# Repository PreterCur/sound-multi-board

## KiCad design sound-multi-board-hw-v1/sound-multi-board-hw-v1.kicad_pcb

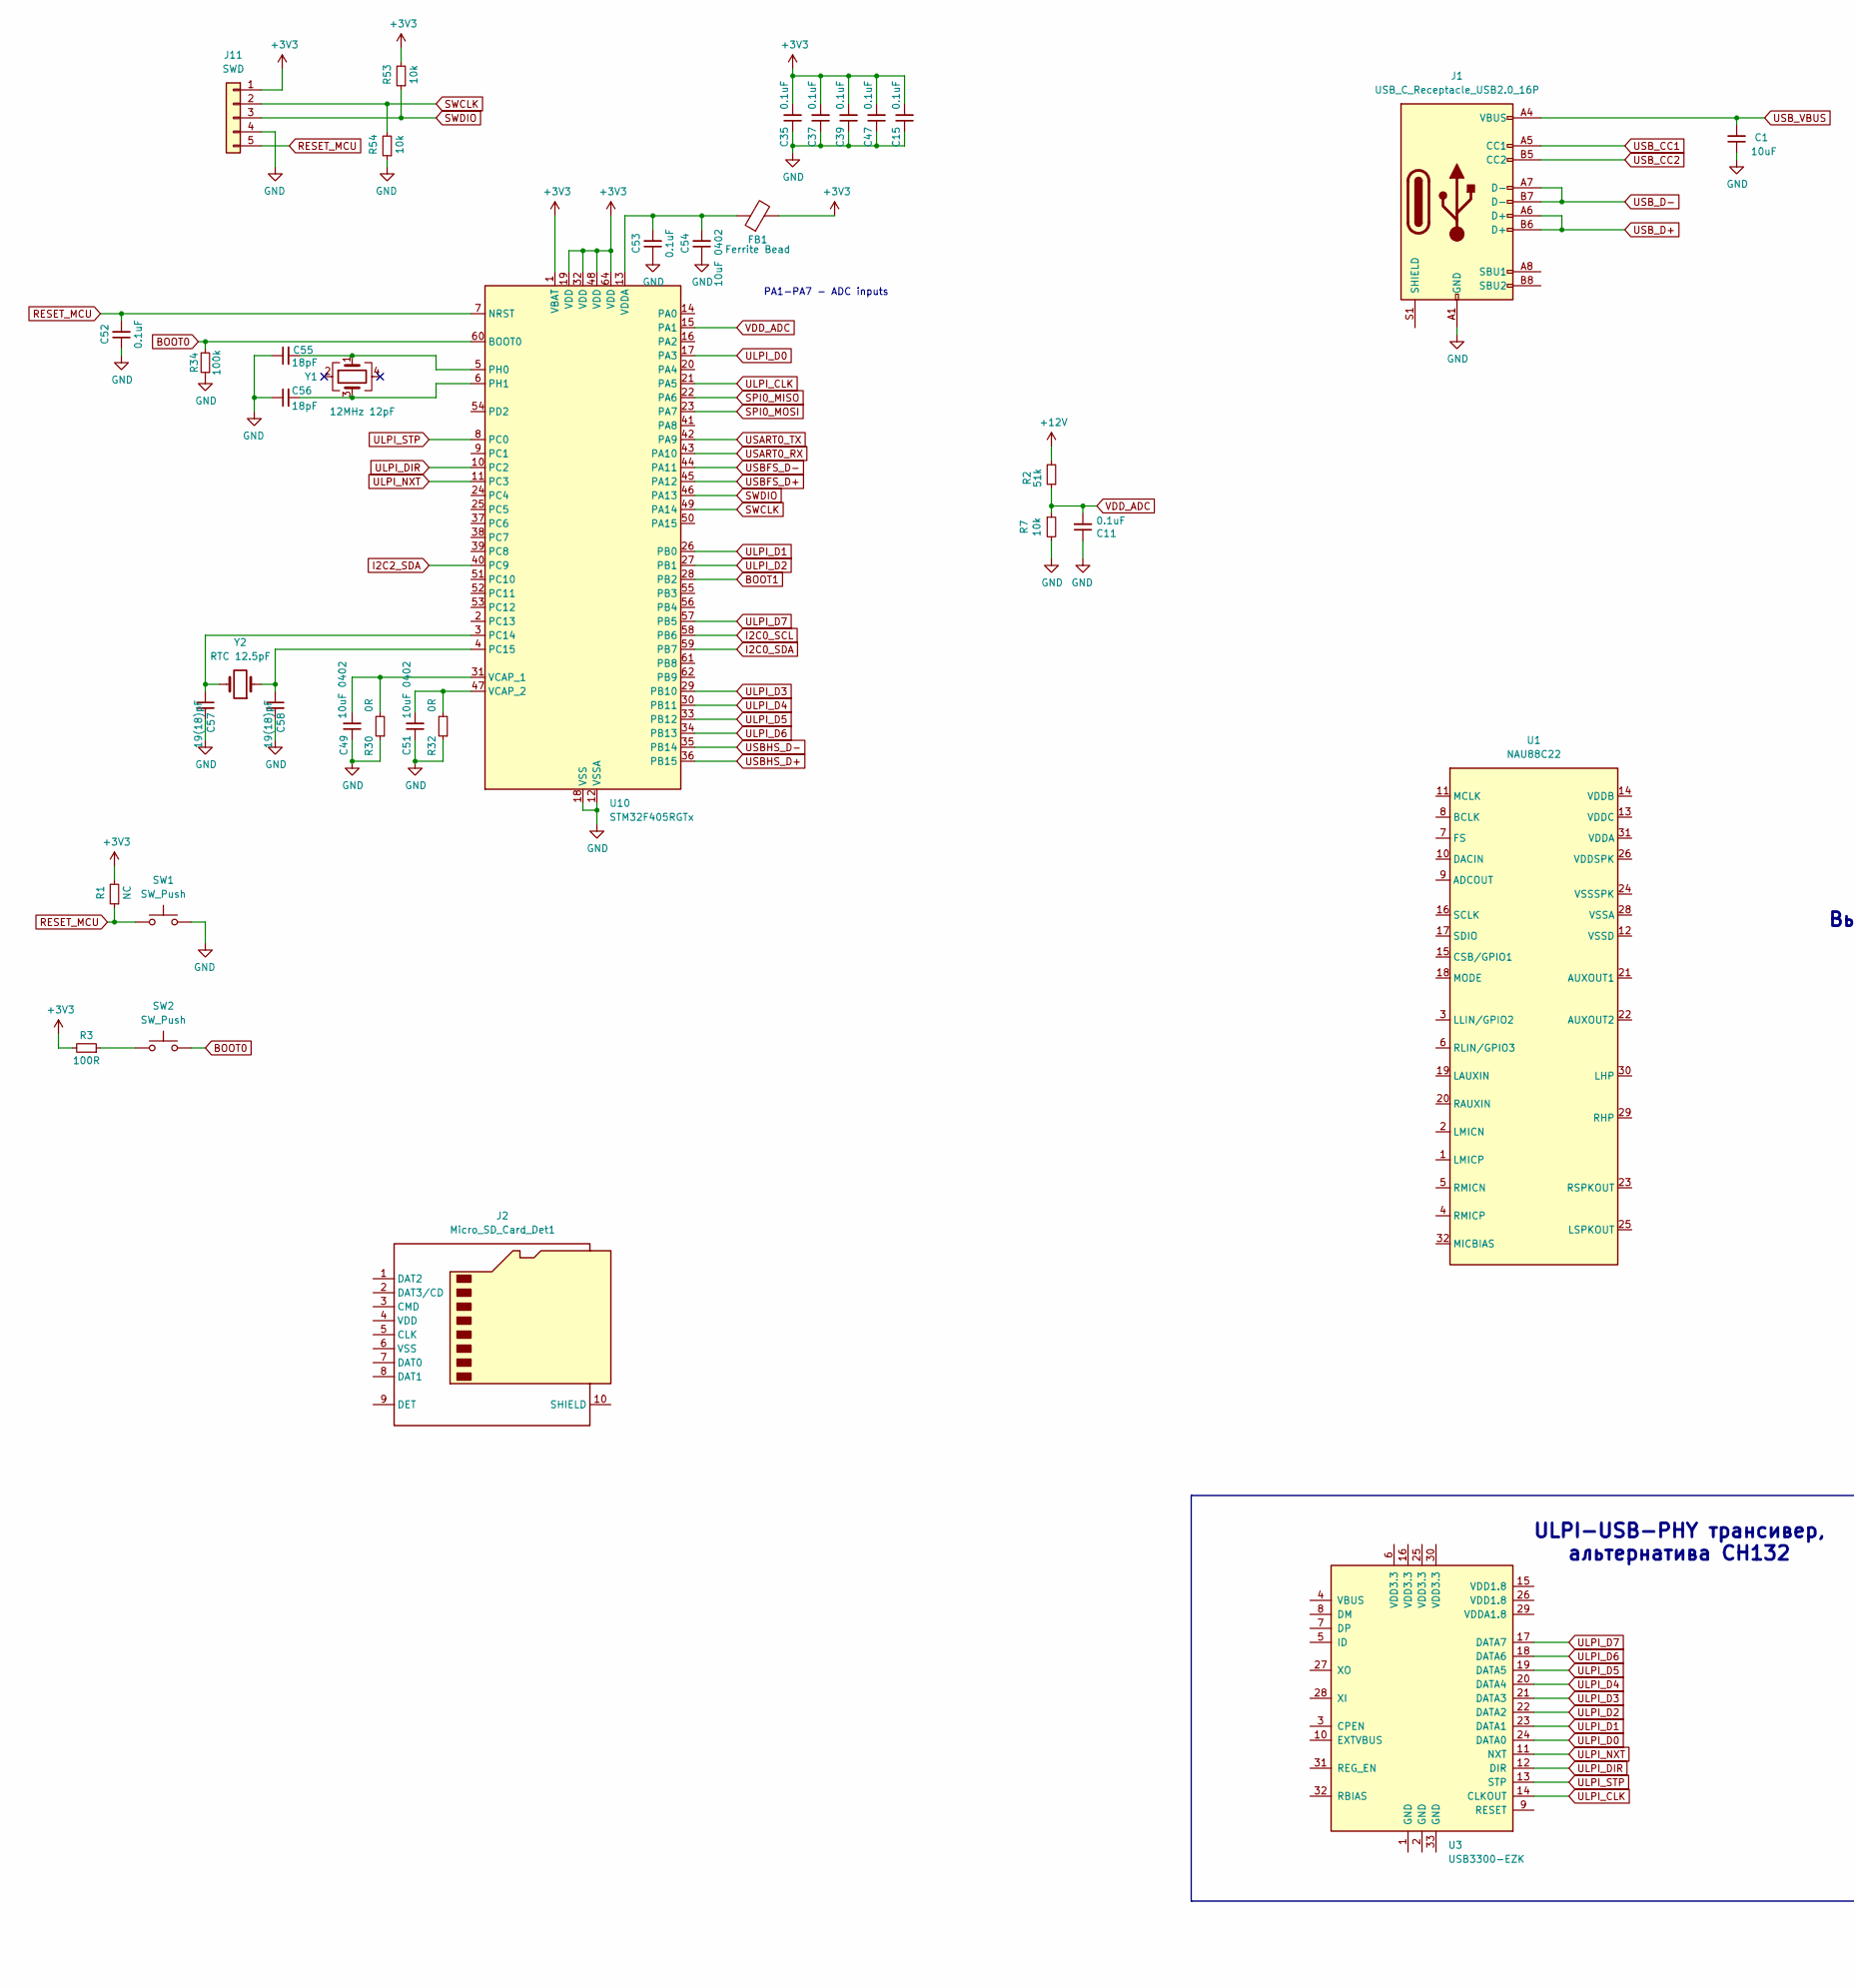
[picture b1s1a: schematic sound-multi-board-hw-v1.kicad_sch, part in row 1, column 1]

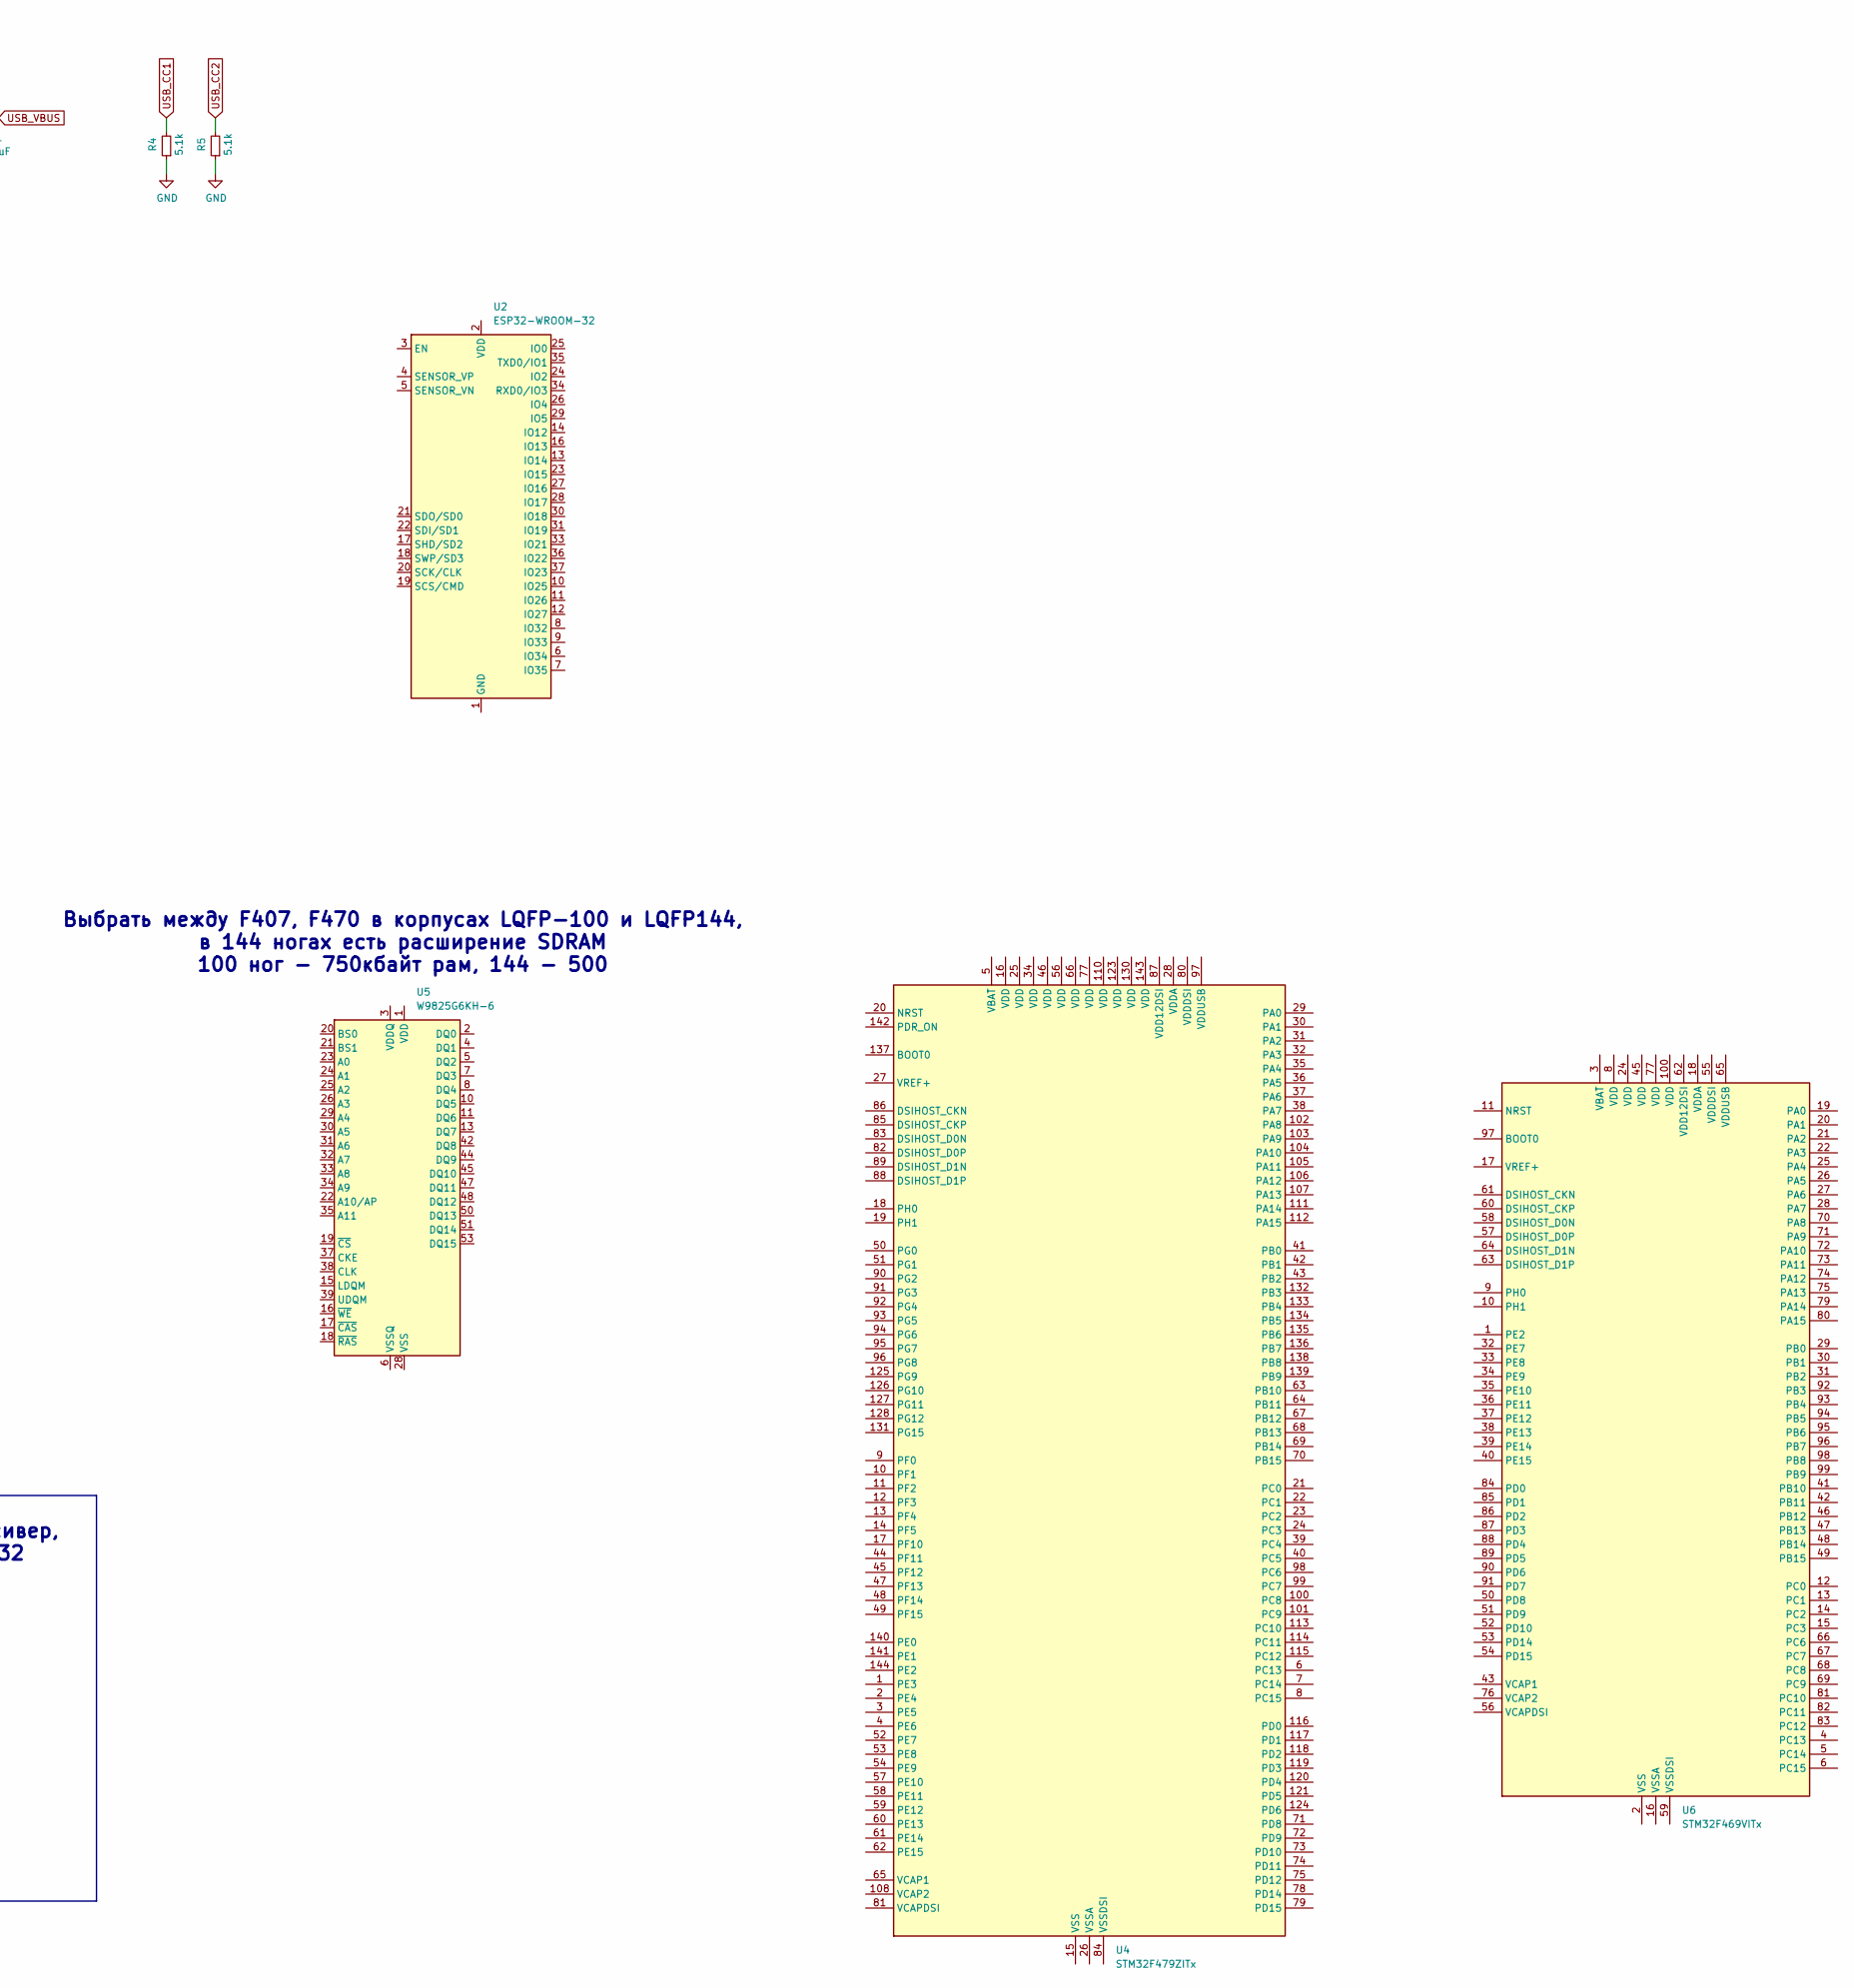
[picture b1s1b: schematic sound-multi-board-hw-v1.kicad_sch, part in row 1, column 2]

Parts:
C1: 10uF; C_0603_1608Metric
C11, C15, C35, C37, C39, C47, C52, C53: 0.1uF; C_0402_1005Metric
C49, C51, C54: 10uF 0402; C_0402_1005Metric
C55, C56: 18pF; C_0402_1005Metric
C57, C58: 19(18)pF; C_0402_1005Metric
FB1: Ferrite Bead; L_0402_1005Metric
J1: USB_C_Receptacle_USB2.0_16P; USB_C_Receptacle_XKB_U262-16XN-4BVC11
J2: Micro_SD_Card_Det1
J11: SWD; PinHeader_1x05_P1.27mm_Vertical
R1: NC; R_0402_1005Metric
R2: 51k; R_0402_1005Metric
R3: 100R; R_0402_1005Metric
R4, R5: 5.1k; R_0402_1005Metric
R7, R53, R54: 10k; R_0402_1005Metric
R30, R32: 0R; R_0402_1005Metric
R34: 100k; R_0402_1005Metric
SW1, SW2: SW_Push
U1: NAU88C22; LFCSP-32-1EP_5x5mm_P0.5mm_EP3.5x3.5mm_ThermalVias
U2: ESP32-WROOM-32
U3: USB3300-EZK; QFN-32-1EP_5x5mm_P0.5mm_EP3.45x3.45mm
U4: STM32F479ZITx; LQFP-144_20x20mm_P0.5mm
U5: W9825G6KH-6; TSOP-II-54_22.2x10.16mm_P0.8mm
U6: STM32F469VITx; LQFP-100_14x14mm_P0.5mm
U10: STM32F405RGTx; LQFP-64_10x10mm_P0.5mm
Y1: 12MHz 12pF; Crystal_SMD_3225-4Pin_3.2x2.5mm
Y2: RTC 12.5pF; Crystal_SMD_3215-2Pin_3.2x1.5mm

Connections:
+3V3: C15.2, C35.2, C37.2, C39.2, C47.2, FB1.2, J11.1, R1.2, R3.2, R53.2, U10.1 (VBAT), U10.19 (VDD), U10.32 (VDD), U10.48 (VDD), U10.64 (VDD)
+12V: R2.2
BOOT0: R34.2, SW2.2, U10.60 (BOOT0)
BOOT1: U10.28 (PB2)
GND: C1.1, C11.1, C15.1, C35.1, C37.1, C39.1, C47.1, C49.1, C51.1, C52.1, C53.1, C54.1, C55.1, C56.1, C57.2, C58.2, J1.A1 (GND), J1.A12 (GND), J1.B1 (GND), J1.B12 (GND), J11.4, R4.1, R5.1, R7.2, R30.1, R32.1, R34.1, R54.1, SW1.2, U10.12 (VSSA), U10.18 (VSS), U10.63 (VSS)
I2C0_SCL: U10.58 (PB6)
I2C0_SDA: U10.59 (PB7)
I2C2_SDA: U10.40 (PC9)
unnamed: R3.1, SW2.1
unnamed: U2.1 (GND), U2.15 (GND), U2.38 (GND), U2.39 (GND)
unnamed: U4.15 (VSS), U4.33 (VSS), U4.55 (VSS), U4.76 (VSS), U4.109 (VSS), U4.122 (VSS), U4.129 (VSS)
unnamed: U5.1 (VDD), U5.14 (VDD), U5.27 (VDD)
unnamed: U5.3 (VDDQ), U5.9 (VDDQ), U5.43 (VDDQ), U5.49 (VDDQ)
unnamed: U5.28 (VSS), U5.41 (VSS), U5.54 (VSS)
unnamed: U5.6 (VSSQ), U5.12 (VSSQ), U5.46 (VSSQ), U5.52 (VSSQ)
unnamed: U6.2 (VSS), U6.7 (VSS), U6.23 (VSS), U6.44 (VSS), U6.78 (VSS)
unnamed: C57.1, U10.3 (PC14), Y2.2
unnamed: C58.1, U10.4 (PC15), Y2.1
unnamed: C55.2, U10.5 (PH0), Y1.1
unnamed: C56.2, U10.6 (PH1), Y1.3
unnamed: C49.2, R30.2, U10.31 (VCAP_1)
unnamed: C51.2, R32.2, U10.47 (VCAP_2)
unnamed: C53.2, C54.2, FB1.1, U10.13 (VDDA)
RESET_MCU: C52.2, J11.5, R1.1, SW1.1, U10.7 (NRST)
SPI0_MISO: U10.22 (PA6)
SPI0_MOSI: U10.23 (PA7)
SWCLK: J11.2, R54.2, U10.49 (PA14)
SWDIO: J11.3, R53.1, U10.46 (PA13)
ULPI_CLK: U3.14 (CLKOUT), U10.21 (PA5)
ULPI_D0: U3.24 (DATA0), U10.17 (PA3)
ULPI_D1: U3.23 (DATA1), U10.26 (PB0)
ULPI_D2: U3.22 (DATA2), U10.27 (PB1)
ULPI_D3: U3.21 (DATA3), U10.29 (PB10)
ULPI_D4: U3.20 (DATA4), U10.30 (PB11)
ULPI_D5: U3.19 (DATA5), U10.33 (PB12)
ULPI_D6: U3.18 (DATA6), U10.34 (PB13)
ULPI_D7: U3.17 (DATA7), U10.57 (PB5)
ULPI_DIR: U3.12 (DIR), U10.10 (PC2)
ULPI_NXT: U3.11 (NXT), U10.11 (PC3)
ULPI_STP: U3.13 (STP), U10.8 (PC0)
USART0_RX: U10.43 (PA10)
USART0_TX: U10.42 (PA9)
USBFS_D+: U10.45 (PA12)
USBFS_D-: U10.44 (PA11)
USBHS_D+: U10.36 (PB15)
USBHS_D-: U10.35 (PB14)
USB_CC1: J1.A5 (CC1), R4.2
USB_CC2: J1.B5 (CC2), R5.2
USB_D+: J1.A6 (D+), J1.B6 (D+)
USB_D-: J1.A7 (D-), J1.B7 (D-)
USB_VBUS: C1.2, J1.A4 (VBUS), J1.A9 (VBUS), J1.B4 (VBUS), J1.B9 (VBUS)
VDD_ADC: C11.2, R2.1, R7.1, U10.15 (PA1)

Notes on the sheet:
PA1-PA7 - ADC inputs
Выбрать между F407, F470 в корпусах LQFP-100 и LQFP144, в 144 ногах есть расширение SDRAM 100 ног - 750кбайт рам, 144 - 500
ULPI-USB-PHY трансивер, альтернатива CH132

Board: 2 copper layers, 39 parts (0 on the bottom side), 38 nets, no tracks yet.

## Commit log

2025-09-07 added gd32 with external ram
2025-09-07 choose between lqfp100 and 144
